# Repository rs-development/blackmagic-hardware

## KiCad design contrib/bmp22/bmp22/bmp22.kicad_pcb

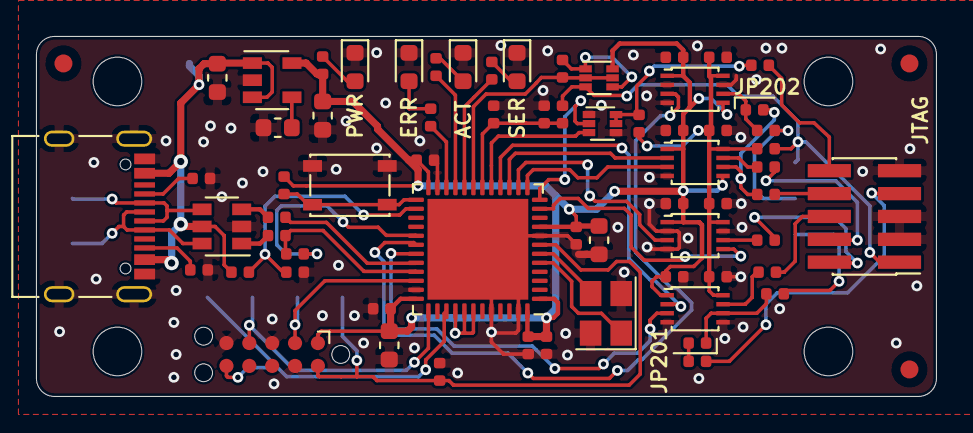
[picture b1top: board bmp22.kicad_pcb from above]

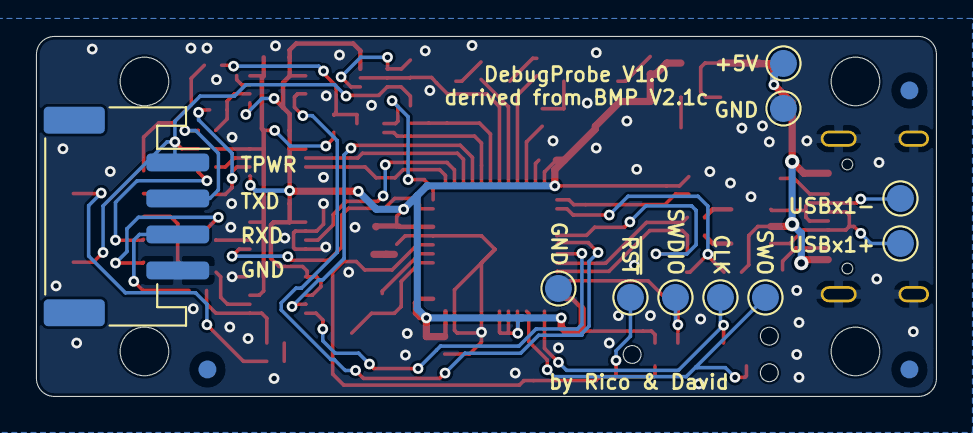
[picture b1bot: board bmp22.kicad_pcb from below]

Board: 2 copper layers, 50.0 x 20.0 mm, 85 parts (13 on the bottom side), 58 nets.

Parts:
C101, C103, C308: 1u; C_0603_1608Metric
C102: TBD; C_0603_1608Metric
C201, C202, C203, C204, C205, C206, C207, C208, C301, C302, C303, C304, C305, C306, C309: 100n; C_0402_1005Metric
C307: 4u7; C_0603_1608Metric
D301: GREEN; LED_0603_1608Metric
D302: RED; LED_0603_1608Metric
D303: ORANGE; LED_0603_1608Metric
D304: YELLOW; LED_0603_1608Metric
FID1, FID2, FID3, FID4, FID5, FID6: Fiducial; Fiducial_1mm_Mask2mm
H1, H2, H3, H4: MountingHole; MountingHole_2.7mm_M2.5_DIN965
J201: Conn_01x10_Male; PinHeader_2x05_P1.27mm_Vertical_SMD
J202: PH1x4; JST_PH_S4B-PH-SM4-TB_1x04-1MP_P2.00mm_Horizontal
J301: USB_C_Receptacle_USB2.0; USB_C_Receptacle_Palconn_UTC16-G
J302: Conn_ARM_JTAG_SWD_10; Tag-Connect_TC2050-IDC-NL_2x05_P1.27mm_Vertical
JP201: RX-KEY; R_0402_1005Metric
JP202: TX-TDI; R_0402_1005Metric
Q201: DMG1023UV-7; SOT-563
Q203: DMG1024UV-7; SOT-563
R201, R202, R203, R204, R205, R206, R207, R208, R209: 100; R_0402_1005Metric
R210, R211, R305, R308, R310: 10k; R_0402_1005Metric
R301, R303: 22; R_0402_1005Metric
R302, R304: 4k7; R_0402_1005Metric
R306, R307: 5k1; R_0402_1005Metric
R309: 1k5; R_0402_1005Metric
R311, R312, R313, R314: 330; R_0402_1005Metric
SW301: SW_DIP_x01; SW_SPST_PTS810
TP301: ~RST; TestPoint_Pad_D1.5mm
TP302: +5V; TestPoint_Pad_D1.5mm
TP303: USBx1-; TestPoint_Pad_D1.5mm
TP304: USBx1+; TestPoint_Pad_D1.5mm
TP305, TP309: GND; TestPoint_Pad_D1.5mm
TP306: SWO; TestPoint_Pad_D1.5mm
TP307: CLK; TestPoint_Pad_D1.5mm
TP308: SWDIO; TestPoint_Pad_D1.5mm
U101: LP2985-3.3; SOT-23-5
U201, U202, U203, U204: SN74LVC2T45DCUR; VSSOP-8_2.4x2.1mm_P0.5mm
U301: USBLC6-2SC6; SOT-23-6
U302: STM32F103CBUx; QFN-48-1EP_7x7mm_P0.5mm_EP5.6x5.6mm
Y301: 8MHz; Crystal_SMD_3225-4Pin_3.2x2.5mm

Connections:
+3V3: C103.1, C201.1, C203.1, C205.1, C207.1, C302.1, C303.1, C304.1, C305.1, C306.1, C307.1, C308.1, J302.1, Q201.6, R310.1, R311.1, U101.5, U201.1, U201.5, U202.1, U202.5, U203.1, U204.1, U302.1, U302.9, U302.24, U302.36, U302.40, U302.41, U302.42, U302.48
+5V: C101.1, J301.A4, J301.A9, J301.B4, J301.B9, R302.1, TP302.1, U101.1, U101.3, U301.5
/Sheet5F21D67E/RXD: J202.3, R209.1
/Sheet5F21D67E/TXD: J202.2, R208.1
/Sheet5F25207C/HSE_IN: U302.5, Y301.1
/Sheet5F25207C/HSE_OUT: U302.6, Y301.3
/Sheet5F25207C/LED0: R312.1, U302.20
/Sheet5F25207C/LED1: R313.1, U302.21
/Sheet5F25207C/LED2: R314.1, U302.22
/Sheet5F25207C/SDWIO: J302.2, TP308.1, U302.34
/Sheet5F25207C/SWDCLK: J302.4, TP307.1, U302.37
/Sheet5F25207C/TRACESWO: J302.6, TP306.1, U302.39
/Sheet5F25207C/USB_N: R303.1, U302.32
/Sheet5F25207C/USB_P: R301.1, R309.1, U302.33
/Sheet5F25207C/USBx1+: J301.A6, J301.B6, TP304.1, U301.6
/Sheet5F25207C/USBx1-: J301.A7, J301.B7, TP303.1, U301.4
/Sheet5F25207C/USBx2+: R301.2, U301.1
/Sheet5F25207C/USBx2-: R303.2, U301.3
/Sheet5F25207C/VBUS: R302.2, R308.1, U302.26
/Sheet5F25207C/~RST: C301.1, J302.10, TP301.1, U302.7
GND: C101.2, C102.2, C103.2, C201.2, C202.2, C203.2, C204.2, C205.2, C206.2, C207.2, C208.2, C301.2, C302.2, C303.2, C304.2, C305.2, C306.2, C307.2, C308.2, C309.2, D301.1, D302.1, D303.1, D304.1, J201.3, J201.5, J201.9, J202.4, J301.A1, J301.A12, J301.B1, J301.B12, J301.S1, J302.3, J302.5, J302.9, Q203.1, Q203.4, R305.2, R306.2, R307.2, R308.2, SW301.2, TP305.1, TP309.1, U101.2, U201.2, U201.4, U201.7, U202.4, U203.4, U203.5, U204.2, U204.4, U204.7, U301.2, U302.8, U302.23, U302.35, U302.44, U302.47, U302.49, Y301.2, Y301.4
KEY: J201.7, R205.1
unnamed: C102.1, U101.4
unnamed: C309.1, R304.2, R305.1, U302.18
unnamed: D301.2, R311.2
unnamed: D302.2, R312.2
unnamed: D303.2, R313.2
unnamed: D304.2, R314.2
unnamed: J301.A5, R307.1
unnamed: J301.B5, R306.1
unnamed: Q201.1, Q201.4, R210.1
unnamed: R309.2, U302.29
unnamed: R310.2, SW301.1, U302.25
PWR_BR: Q201.2, Q201.5, R210.2, U302.19
RST: J201.10, R207.1
TCK: J201.4, R203.1
TDI: J201.8, R206.1
TDO: J201.6, R204.1
TMS: J201.2, R202.1
TPWR: J201.1, J202.1, Q201.3, R201.1, R304.1
iRST: Q203.2, U302.12
iRST_SENSE: Q203.3, U302.17
iRXD: U203.3, U302.31
iTCK: U202.2, U302.15
iTDI: U202.3, U302.13
iTDO: U203.2, U302.16
iTMS: U204.3, U302.14
iTMS_DIR: U204.5, U302.11
iTXD: U201.3, U302.30
xKEY: JP201.2, R205.2
xRST: Q203.5, Q203.6, R207.2, R211.1
xRXD: JP201.1, R209.2, U203.6
xTCK: R203.2, U202.7
xTDI: JP202.2, R206.2, U202.6
xTDO: R204.2, U203.7
xTMS: R202.2, U204.6
xTPWR: C202.1, C204.1, C206.1, C208.1, R201.2, R211.2, U201.8, U202.8, U203.8, U204.8
xTXD: JP202.1, R208.2, U201.6

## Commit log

2020-08-07 updated silkscreen
